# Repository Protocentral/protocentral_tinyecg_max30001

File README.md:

# ProtoCentral tinyECG MAX30001G ECG & Respiration monitoring module

## Don't have one? [Buy it here](https://protocentral.com/product/protocentral-tinyecg-max30001-ecg-respiration-module-for-qt-py-xiao/)

ProtoCentral tinyECG MAX30001G ECG & Respiration monitoring module is a tiny module based on the Analog Devices MAX30001 ECG and Respiration sensor. It is a single lead ECG and Respiration sensor with a built-in amplifier, front-end and ADC. It can be used to measure ECG and Respiration signals from the human body. 

The form factor of the module is designed to fit the [Adafruit QT Py](https://www.adafruit.com/category/595) or[Seeed Studio XIAO](https://wiki.seeedstudio.com/Seeeduino-XIAO/) series of microcontroller boards. These boards offers a tiny form factor with a built-in USB port and a battery connector and are based on your choice of a multitude of microcontrollers . Coupled with one of these boards, you can build a tiny wearable ECG and Respiration monitoring device.

## Hardware Setup

Connection with the Adafruit QT PY ESP32-C3 is as follows:

|Tiny ECG pin label| Adafruit QT PY ESP32-C3 Connection   |Pin Function      |
|----------------- |:--------------------:|-----------------:|
| MISO             | MISO                  |  Slave out|             
| MOSI             | MOSI                  |  Slave in           |
| SCK              | SCK                  |  Serial clock     |
| CS0              | 6                   |  Slave select|
| FCLK             | NC                   |  External clock     |
| INT1             | A0                   |  Interrupt        |
| INT2             | NC                   |  Interrupt       |
| Vcc              | +5V             | Power Supply            |
| GND              | GND                  | GND

# Visualizing Output

## For further details, refer [the documentation on TinyECG module](https://docs.protocentral.com/getting-started-with-tinyECG/)

License Information
===================

This product is open source! Both, our hardware and software are open source and licensed under the following licenses:

Hardware
---------

**All hardware is released under the [CERN-OHL-P v2](https://ohwr.org/cern_ohl_p_v2.txt)** license.

Copyright CERN 2020.

This source describes Open Hardware and is licensed under the CERN-OHL-P v2.

You may redistribute and modify this documentation and make products
using it under the terms of the CERN-OHL-P v2 (https:/cern.ch/cern-ohl).
This documentation is distributed WITHOUT ANY EXPRESS OR IMPLIED
WARRANTY, INCLUDING OF MERCHANTABILITY, SATISFACTORY QUALITY
AND FITNESS FOR A PARTICULAR PURPOSE. Please see the CERN-OHL-P v2
for applicable conditions

Software
--------

**All software is released under the MIT License(http://opensource.org/licenses/MIT).**

THE SOFTWARE IS PROVIDED "AS IS", WITHOUT WARRANTY OF ANY KIND, EXPRESS OR IMPLIED, INCLUDING BUT NOT LIMITED TO THE WARRANTIES OF MERCHANTABILITY, FITNESS FOR A PARTICULAR PURPOSE AND NONINFRINGEMENT. IN NO EVENT SHALL THE AUTHORS OR COPYRIGHT HOLDERS BE LIABLE FOR ANY CLAIM, DAMAGES OR OTHER LIABILITY, WHETHER IN AN ACTION OF CONTRACT, TORT OR OTHERWISE, ARISING FROM, OUT OF OR IN CONNECTION WITH THE SOFTWARE OR THE USE OR OTHER DEALINGS IN THE SOFTWARE.

Documentation
-------------
**All documentation is released under [Creative Commons Share-alike 4.0 International](http://creativecommons.org/licenses/by-sa/4.0/).**

You are free to:

* Share — copy and redistribute the material in any medium or format
* Adapt — remix, transform, and build upon the material for any purpose, even commercially.
The licensor cannot revoke these freedoms as long as you follow the license terms.

Under the following terms:

* Attribution — You must give appropriate credit, provide a link to the license, and indicate if changes were made. You may do so in any reasonable manner, but not in any way that suggests the licensor endorses you or your use.
* ShareAlike — If you remix, transform, or build upon the material, you must distribute your contributions under the same license as the original.

Please check [*LICENSE.md*](LICENSE.md) for detailed license descriptions.

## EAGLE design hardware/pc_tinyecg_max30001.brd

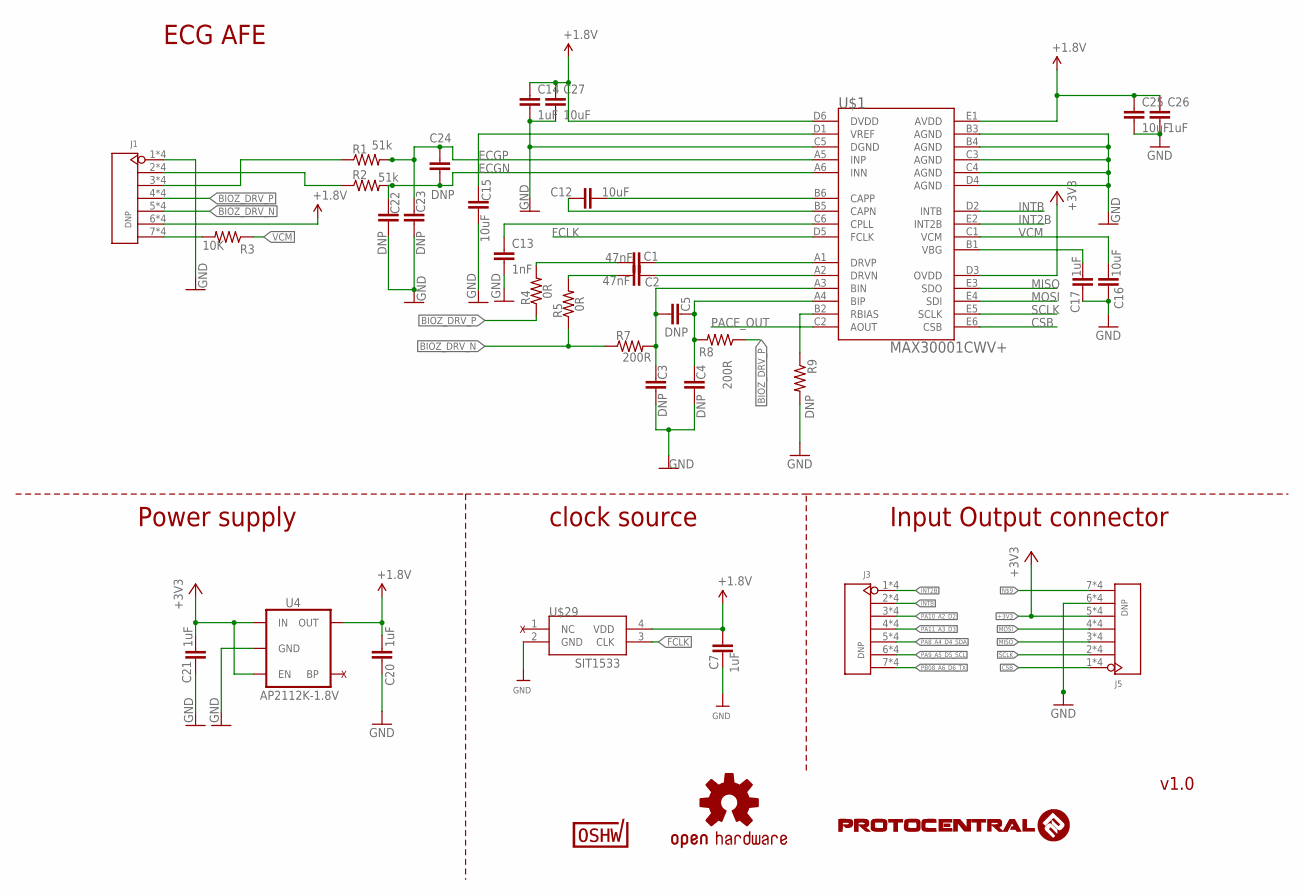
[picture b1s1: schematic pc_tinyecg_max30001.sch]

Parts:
C1, C2: 47nF; C0402
C3, C4, C5, C22, C23, C24: DNP; C0402
C7, C14, C17, C20, C21, C26: 1uF; C0402
C12, C15, C16, C25, C27: 10uF; C0402
C13: 1nF; C0402
J1, J3, J5: DNP; H7-HALF-HOLE-2.54
R1, R2: 51k; 0402-RES
R3: 10K; 0402-RES
R4, R5: 0R; 0402-RES
R7, R8: 200R; 0402-RES
R9: DNP; 0402-RES
U4: AP2112K-1.8V; SOT23-5
U$1: MAX30001CWV+; 30WLP
U$14: OSHW-LOGOM; OSHW-LOGO-M
U$29: SIT1533
U$35: CERT-SMALL; CERT-SMALL-SILK

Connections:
+1.8V: C7.2, C14.1, C20.2, C25.1, C26.1, C27.1, J1.6, J1.18 (6), J1.P$6 (6), J1.P$9 (6), U4.5 (OUT), U$1.D6 (DVDD), U$1.E1 (AVDD), U$29.4 (VDD)
+3V3: C21.2, J5.5, J5.17 (5), J5.P$5 (5), J5.P$10 (5), U4.1 (IN), U4.3 (EN), U$1.D3 (OVDD)
BIOZ_DRV_N: J1.5, J1.17 (5), J1.P$5 (5), J1.P$10 (5), R5.1, R7.1
BIOZ_DRV_P: J1.4, J1.16 (4), J1.P$4 (4), J1.P$11 (4), R4.1, R8.1
CSB: J5.1, J5.13 (1), J5.P$1 (1), J5.P$14 (1), U$1.E6 (CSB)
ECGN: C22.1, C24.2, R2.2, U$1.A6 (INN)
ECGN1: J1.2, J1.14 (2), J1.P$2 (2), J1.P$13 (2), R2.1
ECGP: C23.1, C24.1, R1.2, U$1.A5 (INP)
ECGP1: J1.3, J1.15 (3), J1.P$3 (3), J1.P$12 (3), R1.1
FCLK: U$1.D5 (FCLK), U$29.3 (CLK)
GND: C3.2, C4.2, C7.1, C13.2, C14.2, C15.2, C16.2, C17.2, C20.1, C21.1, C22.2, C23.2, C25.2, C26.2, C27.2, J1.1, J1.13 (1), J1.P$1 (1), J1.P$14 (1), J5.6, J5.18 (6), J5.P$6 (6), J5.P$9 (6), R9.2, U4.2 (GND), U$1.B3 (AGND), U$1.B4 (AGND), U$1.C3 (AGND), U$1.C4 (AGND), U$1.C5 (DGND), U$1.D4 (AGND), U$29.2 (GND)
INT2B: J3.1, J3.13 (1), J3.P$1 (1), J3.P$14 (1), U$1.E2 (INT2B)
INTB: J3.2, J3.14 (2), J3.P$2 (2), J3.P$13 (2), U$1.D2 (INTB)
MISO: J5.3, J5.15 (3), J5.P$3 (3), J5.P$12 (3), U$1.E3 (SDO)
MOSI: J5.4, J5.16 (4), J5.P$4 (4), J5.P$11 (4), U$1.E4 (SDI)
unnamed: C12.1, U$1.B6 (CAPP)
unnamed: C1.2, U$1.A1 (DRVP)
unnamed: C2.1, R5.2
unnamed: C2.2, U$1.A2 (DRVN)
unnamed: C3.1, C5.1, R7.2, U$1.A3 (BIN)
unnamed: C4.1, C5.2, R8.2, U$1.A4 (BIP)
unnamed: R9.1, U$1.B2 (RBIAS)
unnamed: J1.7, J1.19 (7), J1.P$7 (7), J1.P$8 (7), R3.2
unnamed: J5.7, J5.19 (7), J5.P$7 (7), J5.P$8 (7)
unnamed: C13.1, U$1.C6 (CPLL)
unnamed: C1.1, R4.2
unnamed: C12.2, U$1.B5 (CAPN)
unnamed: C15.1, U$1.D1 (VREF)
unnamed: C17.1, U$1.B1 (VBG)
PA8_A4_D4_SDA: J3.5, J3.17 (5), J3.P$5 (5), J3.P$10 (5)
PA9_A5_D5_SCL: J3.6, J3.18 (6), J3.P$6 (6), J3.P$9 (6)
PA10_A2_D2: J3.3, J3.15 (3), J3.P$3 (3), J3.P$12 (3)
PA11_A3_D3: J3.4, J3.16 (4), J3.P$4 (4), J3.P$11 (4)
PACE_OUT: U$1.C2 (AOUT)
PB08_A6_D6_TX: J3.7, J3.19 (7), J3.P$7 (7), J3.P$8 (7)
SCLK: J5.2, J5.14 (2), J5.P$2 (2), J5.P$13 (2), U$1.E5 (SCLK)
VCM: C16.1, R3.1, U$1.C1 (VCM)

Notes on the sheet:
v1.0
Power supply
clock source
Input Output connector
ECG AFE

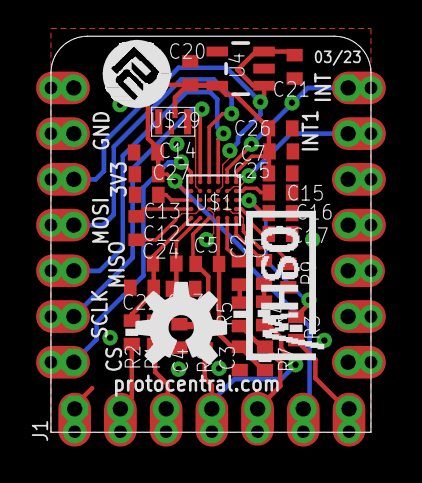
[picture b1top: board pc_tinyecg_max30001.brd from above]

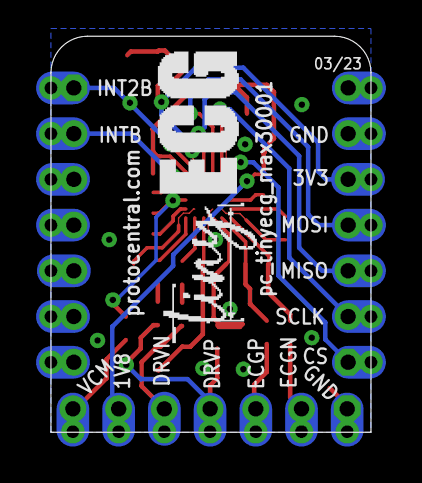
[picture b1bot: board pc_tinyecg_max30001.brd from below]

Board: 2 copper layers, 17.8 x 22.0 mm, 38 parts (3 on the bottom side), 36 nets.

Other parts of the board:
U$4: TNYECG_LOGO
U$5: PCROUNDLOGO

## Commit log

2023-05-02 Add hardware files
2023-05-02 Updated image
2024-11-26 added example code from max30001
2025-02-01 TinyECG compatiable with QT PY
2025-02-03 code updated
2025-04-29 github workflow and readme added
2025-04-29 compile-examples.yml corrected

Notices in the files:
README.md:
CC-BY-SA-4.0
parts and their libraries:
SparkFun-PowerIC: Licensing: Creative Commons ShareAlike 4.0 International - https://creativecommons.org/licenses/by-sa/4.0
microbuilder: This work is placed in the public domain, and may be freely used for commercial and non-commercial work with the following conditions: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
